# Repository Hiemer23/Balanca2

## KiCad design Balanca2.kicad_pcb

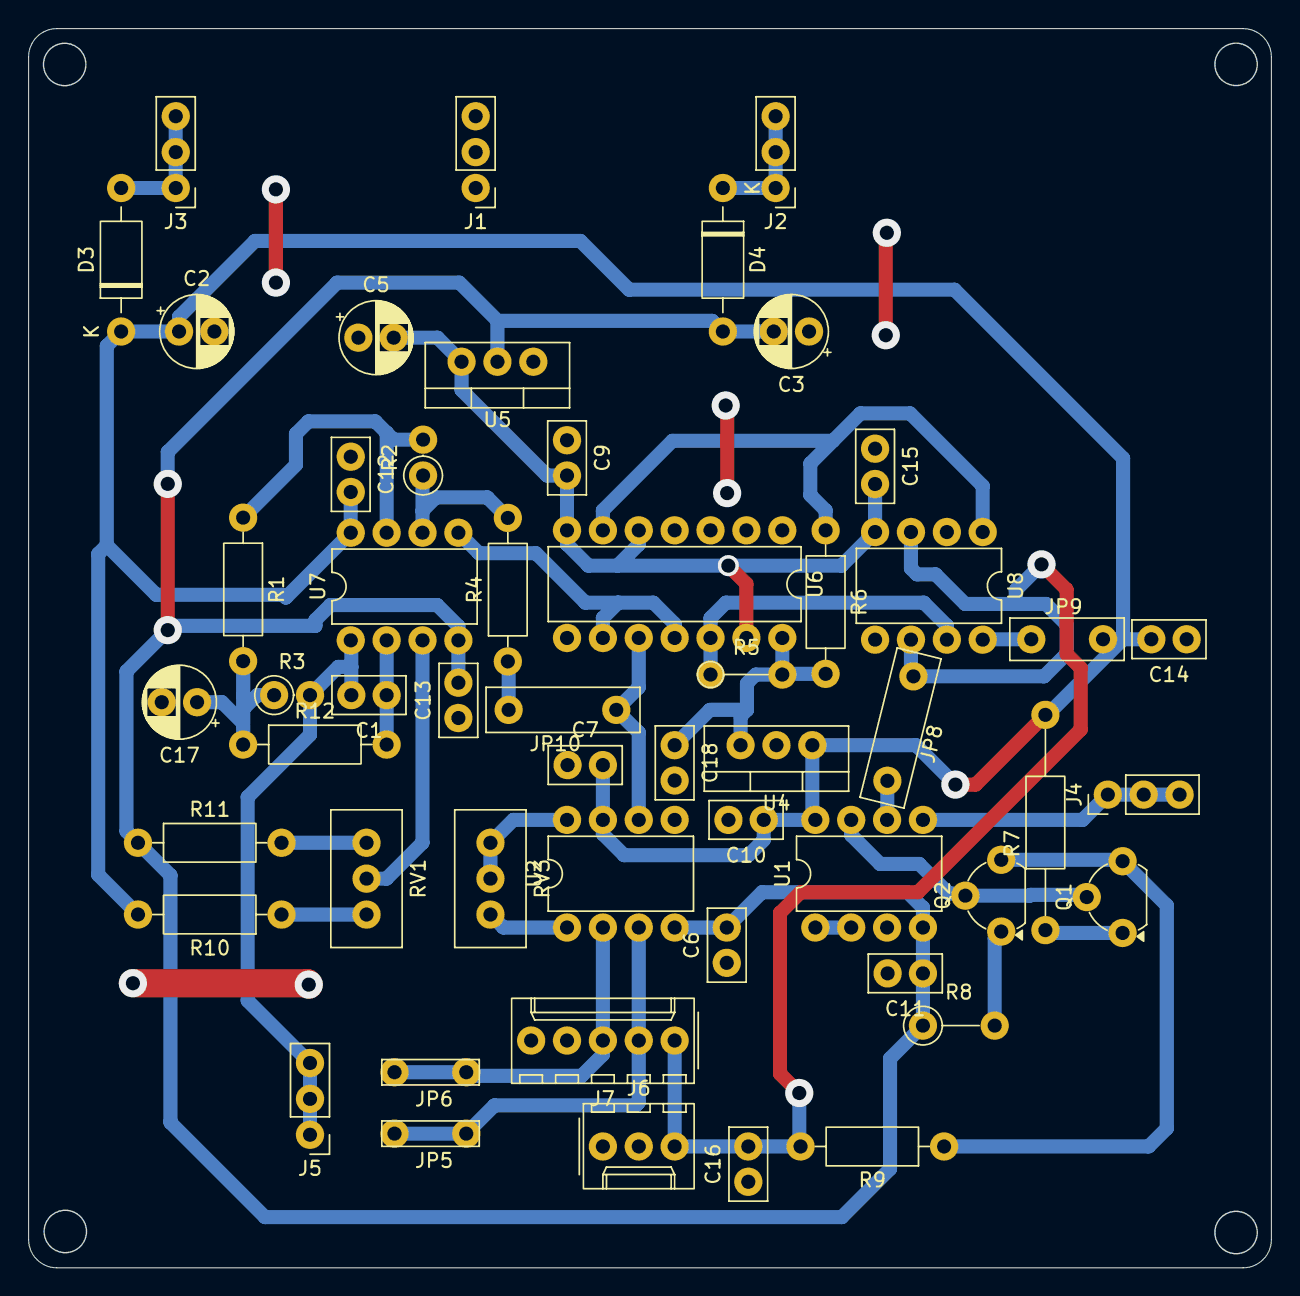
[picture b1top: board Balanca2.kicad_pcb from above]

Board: 2 copper layers, 87.9 x 87.7 mm, 53 parts (0 on the bottom side), 32 nets.

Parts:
C1: 470n; C_Disc_D5.0mm_W2.5mm_P2.50mm
C2, C3: 1u; CP_Radial_D5.0mm_P2.50mm
C5: C_Polarized; CP_Radial_D5.0mm_P2.50mm
C6, C7, C9, C10, C11, C12, C13, C14, C15, C18: 100n; C_Disc_D5.0mm_W2.5mm_P2.50mm
C16: 33p; C_Disc_D5.0mm_W2.5mm_P2.50mm
C17: 4,7u; CP_Radial_D5.0mm_P2.50mm
D3, D4: 1N4007; D_DO-41_SOD81_P10.16mm_Horizontal
J1, J2, J3, J4, J5: Conn_01x03_Pin; PinHeader_1x03_P2.54mm_Vertical
J6: Conn_01x03; Molex_KK-254_AE-6410-03A_1x03_P2.54mm_Vertical
J7: Conn_01x05; Molex_KK-254_AE-6410-05A_1x05_P2.54mm_Vertical
JP5, JP6: Jumper_2_Bridged; TestPoint_Bridge_Pitch5.08mm_Drill0.7mm
JP8, JP10: Jumper_2_Bridged; TestPoint_Bridge_Pitch7.62mm_Drill1.3mm
JP9: Jumper_2_Bridged; TestPoint_Bridge_Pitch5.08mm_Drill1.3mm
Q1: BC547; TO-92L_Wide
Q2: BC557; TO-92L_Wide
R1, R4, R6, R12: 10k; R_Axial_DIN0207_L6.3mm_D2.5mm_P10.16mm_Horizontal
R2: 10k; R_Axial_DIN0207_L6.3mm_D2.5mm_P2.54mm_Vertical
R3: 47k; R_Axial_DIN0207_L6.3mm_D2.5mm_P2.54mm_Vertical
R5: 10k; R_Axial_DIN0204_L3.6mm_D1.6mm_P5.08mm_Vertical
R7: 330; R_Axial_DIN0207_L6.3mm_D2.5mm_P15.24mm_Horizontal
R8: 330; R_Axial_DIN0207_L6.3mm_D2.5mm_P5.08mm_Vertical
R9: 33; R_Axial_DIN0207_L6.3mm_D2.5mm_P10.16mm_Horizontal
R10, R11: 100k; R_Axial_DIN0207_L6.3mm_D2.5mm_P10.16mm_Horizontal
RV1: 10k; Potentiometer_Bourns_3296W_Vertical
RV3: 10K; Potentiometer_Bourns_3296W_Vertical
U1, U7: TL082; DIP-8_W7.62mm
U2: INA128; DIP-8_W7.62mm
U4: LM7805_TO220; TO-220-3_Vertical
U5: LM7905_TO220; TO-220-3_Vertical
U6: CD4066BE; DIP-14_W7.62mm
U8: LM393; DIP-8_W7.62mm

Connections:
+5V: C18.1, R5.2, R6.2, U4.3 (VO), U6.14 (V_{DD})
+15V: C2.1, C7.2, C10.1, C12.2, C14.2, D3.1 (K), JP9.1 (A), R7.2, R10.2, U1.8 (V+), U2.7 (V+), U4.1 (VI), U7.8 (V+)
-5V: C5.2, C9.2, C15.2, U5.3 (VO), U6.5, U6.7 (V_{SS}), U6.13, U8.4 (V-)
-15V: C3.2, C6.2, C11.1, C13.2, D4.2 (A), R8.1, R11.1, U1.4 (V-), U2.4 (V-), U5.2 (VI), U7.4 (V-)
/CelulaCargaAlimentacaoV+: C16.2, J6.3, J7.1, JP8.1 (A), JP8.2 (B), R9.2, U1.6 (-), U8.3 (+), U8.6 (-)
/Controle1: R6.1, U6.6, U8.1
/Controle2: R5.1, U6.12, U8.7
/Entrada+15V: D3.2 (A), J3.1, J3.2, J3.3
/Entrada-15V: D4.1 (K), J2.1, J2.2, J2.3
/SaidaBalanca: C1.2, J5.1, J5.2, J5.3, R3.2, U7.1
/SaidaDemodulada: R1.1, R2.2, U7.7
/SaidaPrimeiroEstagio: JP10.2 (B), U2.6, U6.10
/SaidaPrimeiroEstagioA: JP10.1 (A), R4.1
/SaídaBuffer: Q1.2 (B), Q2.2 (B), U1.7
/SinalSaida+: J7.2, JP5.1 (A_1), U2.3 (+)
/SinalSaida-: J7.3, JP6.1 (A_1), U2.2 (-)
/V_Offset: RV1.2, U7.3 (+)
AC: J4.1, J4.2, J4.3, U1.5 (+)
GND: C2.2, C3.1, C5.1, C6.1, C7.1, C9.1, C10.2, C11.2, C12.1, C13.1, C14.1, C15.1, C16.1, C17.2, C18.2, J1.1, J1.2, J1.3, J6.1, J7.4, U1.3 (+), U2.5 (Ref), U4.2 (GND), U5.1 (GND), U6.1, U6.2, U6.3, U6.4, U6.8, U8.2 (-), U8.5 (+)
unnamed: C17.1, R1.2, R3.1, R12.1
unnamed: JP9.2 (B), U8.8 (V+)
unnamed: Q1.1 (C), R7.1
unnamed: Q1.3 (E), Q2.3 (E), R9.1
unnamed: Q2.1 (C), R8.2
unnamed: R10.1, RV1.1
unnamed: R11.2, RV1.3
unnamed: RV3.1, U2.1 (Rg)
unnamed: RV3.2, RV3.3, U2.8 (Rg)
unnamed: U1.1, U1.2 (-)
unnamed: C1.1, R12.2, U7.2 (-)
unnamed: U6.9, U6.11, U7.5 (+)
unnamed: R2.1, R4.2, U7.6 (-)

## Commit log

2026-06-11 Primeiro commit: Projeto da Balança configurado
2026-06-11 Ajuste inicial da versao 2
2026-06-12 Mudança da placa v2
2026-06-12 Atualizacao da versao 3
2026-06-13 Atualizacao de esquematico da placa 3
2026-06-15 Inicio do Roteamento
2026-06-15 Atualizacao de footprints
2026-06-16 Inicio do novo Roteamento
2026-06-17 Roteamento iniciado, falta verificar erros
2026-06-17 Alteracoes de footprint e melhorias de trilhas
2026-06-17 Finalizada Versao 3
